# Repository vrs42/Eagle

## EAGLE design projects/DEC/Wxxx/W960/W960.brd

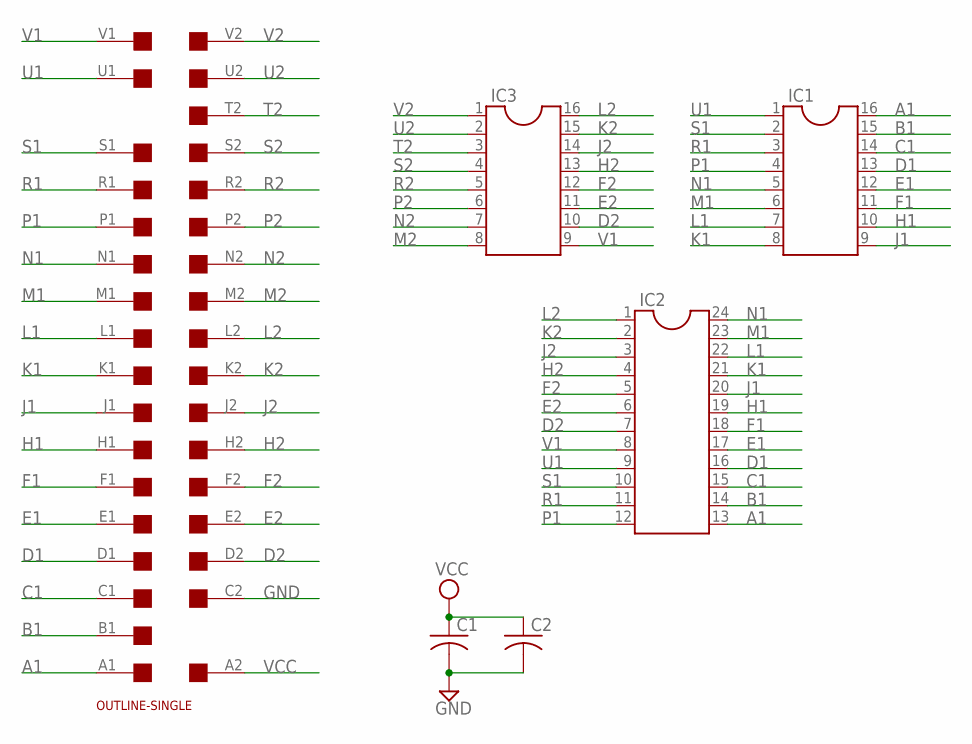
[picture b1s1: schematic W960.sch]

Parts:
C1, C2: C-US050-025X075; C050-025X075
IC1, IC3: DIL16
IC2: DIL24-6
U$1: EDGE-2CONNECTOR; EDGE-CON2
U$2: OUTLINE-SINGLE; SINGLE

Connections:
A1: IC1.16, IC2.13, U$1.A1
B1: IC1.15, IC2.14, U$1.B1
C1: IC1.14, IC2.15, U$1.C1
D1: IC1.13, IC2.16, U$1.D1
D2: IC2.7, IC3.10, U$1.D2
E1: IC1.12, IC2.17, U$1.E1
E2: IC2.6, IC3.11, U$1.E2
F1: IC1.11, IC2.18, U$1.F1
F2: IC2.5, IC3.12, U$1.F2
GND: C1.2, C2.2, U$1.C2
H1: IC1.10, IC2.19, U$1.H1
H2: IC2.4, IC3.13, U$1.H2
J1: IC1.9, IC2.20, U$1.J1
J2: IC2.3, IC3.14, U$1.J2
K1: IC1.8, IC2.21, U$1.K1
K2: IC2.2, IC3.15, U$1.K2
L1: IC1.7, IC2.22, U$1.L1
L2: IC2.1, IC3.16, U$1.L2
M1: IC1.6, IC2.23, U$1.M1
M2: IC3.8, U$1.M2
N1: IC1.5, IC2.24, U$1.N1
N2: IC3.7, U$1.N2
P1: IC1.4, IC2.12, U$1.P1
P2: IC3.6, U$1.P2
R1: IC1.3, IC2.11, U$1.R1
R2: IC3.5, U$1.R2
S1: IC1.2, IC2.10, U$1.S1
S2: IC3.4, U$1.S2
T2: IC3.3, U$1.T2
U1: IC1.1, IC2.9, U$1.U1
U2: IC3.2, U$1.U2
V1: IC2.8, IC3.9, U$1.V1
V2: IC3.1, U$1.V2
VCC: C1.1, C2.1, U$1.A2

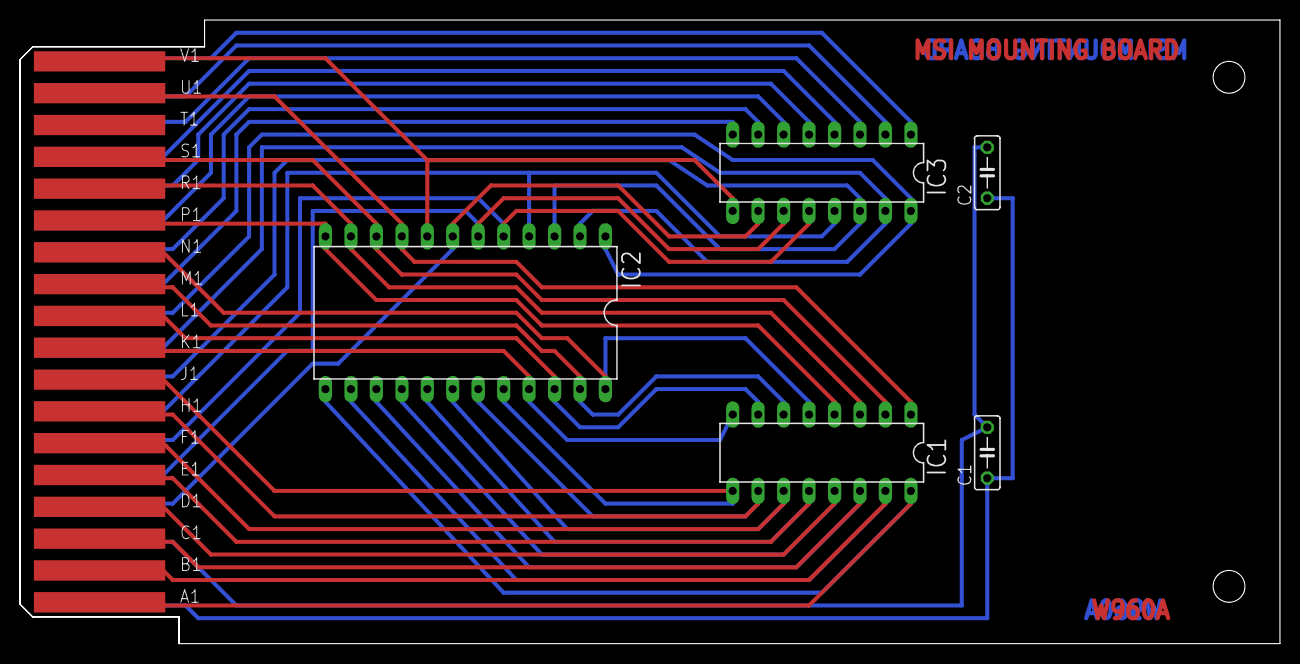
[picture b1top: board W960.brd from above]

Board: 2 copper layers, 125.7 x 62.2 mm, 7 parts (0 on the bottom side), 34 nets.

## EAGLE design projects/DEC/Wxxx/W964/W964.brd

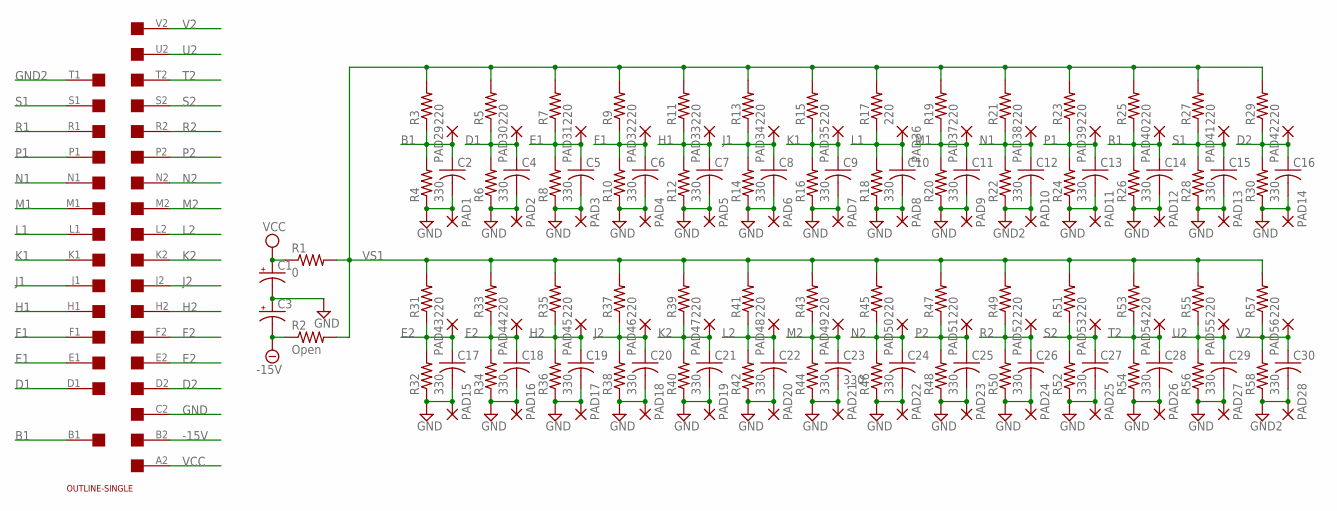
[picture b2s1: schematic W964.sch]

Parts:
C1, C3: CPOL-USE22-6AXIAL; E22-6
C2, C4, C5, C6, C7, C8, C9, C10, C11, C12, C13, C14, C15, C16, C17, C18, C19, C20, C21, C22, C24, C25, C26, C27, C28, C29, C30: C-US050-025X075; C050-025X075
C23: 330; C050-025X075
PAD1, PAD2, PAD3, PAD4, PAD5, PAD6, PAD7, PAD8, PAD9, PAD10, PAD11, PAD12, PAD13, PAD14, PAD15, PAD16, PAD17, PAD18, PAD19, PAD20, PAD21, PAD22, PAD23, PAD24, PAD25, PAD26, PAD27, PAD28, PAD29, PAD30, PAD31, PAD32, PAD33, PAD34, PAD35, PAD36, PAD37, PAD38, PAD39, PAD40, PAD41, PAD42, PAD43, PAD44, PAD45, PAD46, PAD47, PAD48, PAD49, PAD50, PAD51, PAD52, PAD53, PAD54, PAD55, PAD56: 1,6/0,9
R1: 0; 0207/10
R2: Open; 0207/10
R3, R5, R7, R9, R11, R13, R15, R17, R19, R21, R23, R25, R27, R29, R31, R33, R35, R37, R39, R41, R43, R45, R47, R49, R51, R53, R55, R57: 220; 0207/10
R4, R6, R8, R10, R12, R14, R16, R18, R20, R22, R24, R26, R28, R30, R32, R34, R36, R38, R40, R42, R44, R46, R48, R50, R52, R54, R56, R58: 330; 0207/10
U$1: EDGE-2CONNECTOR; EDGE-CON2
U$2: OUTLINE-SINGLE; SINGLE

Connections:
-15V: C3.-, R2.1, U$1.B2
B1: C2.1, PAD29.1, R3.1, R4.2, U$1.B1
D1: C4.1, PAD30.1, R5.1, R6.2, U$1.D1
D2: C16.1, PAD42.1, R29.1, R30.2, U$1.D2
E1: C5.1, PAD31.1, R7.1, R8.2, U$1.E1
E2: C17.1, PAD43.1, R31.1, R32.2, U$1.E2
F1: C6.1, PAD32.1, R9.1, R10.2, U$1.F1
F2: C18.1, PAD44.1, R33.1, R34.2, U$1.F2
GND: C1.-, C2.2, C3.+, C4.2, C5.2, C6.2, C7.2, C8.2, C9.2, C10.2, C11.2, C13.2, C14.2, C15.2, C16.2, C17.2, C18.2, C19.2, C20.2, C21.2, C22.2, C23.2, C24.2, C25.2, C26.2, C27.2, C28.2, C29.2, PAD1.1, PAD2.1, PAD3.1, PAD4.1, PAD5.1, PAD6.1, PAD7.1, PAD8.1, PAD9.1, PAD11.1, PAD12.1, PAD13.1, PAD14.1, PAD15.1, PAD16.1, PAD17.1, PAD18.1, PAD19.1, PAD20.1, PAD21.1, PAD22.1, PAD23.1, PAD24.1, PAD25.1, PAD26.1, PAD27.1, R4.1, R6.1, R8.1, R10.1, R12.1, R14.1, R16.1, R18.1, R20.1, R24.1, R26.1, R28.1, R30.1, R32.1, R34.1, R36.1, R38.1, R40.1, R42.1, R44.1, R46.1, R48.1, R50.1, R52.1, R54.1, R56.1, U$1.C2
GND2: C12.2, C30.2, PAD10.1, PAD28.1, R22.1, R58.1, U$1.T1
H1: C7.1, PAD33.1, R11.1, R12.2, U$1.H1
H2: C19.1, PAD45.1, R35.1, R36.2, U$1.H2
J1: C8.1, PAD34.1, R13.1, R14.2, U$1.J1
J2: C20.1, PAD46.1, R37.1, R38.2, U$1.J2
K1: C9.1, PAD35.1, R15.1, R16.2, U$1.K1
K2: C21.1, PAD47.1, R39.1, R40.2, U$1.K2
L1: C10.1, PAD36.1, R17.1, R18.2, U$1.L1
L2: C22.1, PAD48.1, R41.1, R42.2, U$1.L2
M1: C11.1, PAD37.1, R19.1, R20.2, U$1.M1
M2: C23.1, PAD49.1, R43.1, R44.2, U$1.M2
N1: C12.1, PAD38.1, R21.1, R22.2, U$1.N1
N2: C24.1, PAD50.1, R45.1, R46.2, U$1.N2
P1: C13.1, PAD39.1, R23.1, R24.2, U$1.P1
P2: C25.1, PAD51.1, R47.1, R48.2, U$1.P2
R1: C14.1, PAD40.1, R25.1, R26.2, U$1.R1
R2: C26.1, PAD52.1, R49.1, R50.2, U$1.R2
S1: C15.1, PAD41.1, R27.1, R28.2, U$1.S1
S2: C27.1, PAD53.1, R51.1, R52.2, U$1.S2
T2: C28.1, PAD54.1, R53.1, R54.2, U$1.T2
U2: C29.1, PAD55.1, R55.1, R56.2, U$1.U2
V2: C30.1, PAD56.1, R57.1, R58.2, U$1.V2
VCC: C1.+, R1.1, U$1.A2
VS1: R1.2, R2.2, R3.2, R5.2, R7.2, R9.2, R11.2, R13.2, R15.2, R17.2, R19.2, R21.2, R23.2, R25.2, R27.2, R29.2, R31.2, R33.2, R35.2, R37.2, R39.2, R41.2, R43.2, R45.2, R47.2, R49.2, R51.2, R53.2, R55.2, R57.2

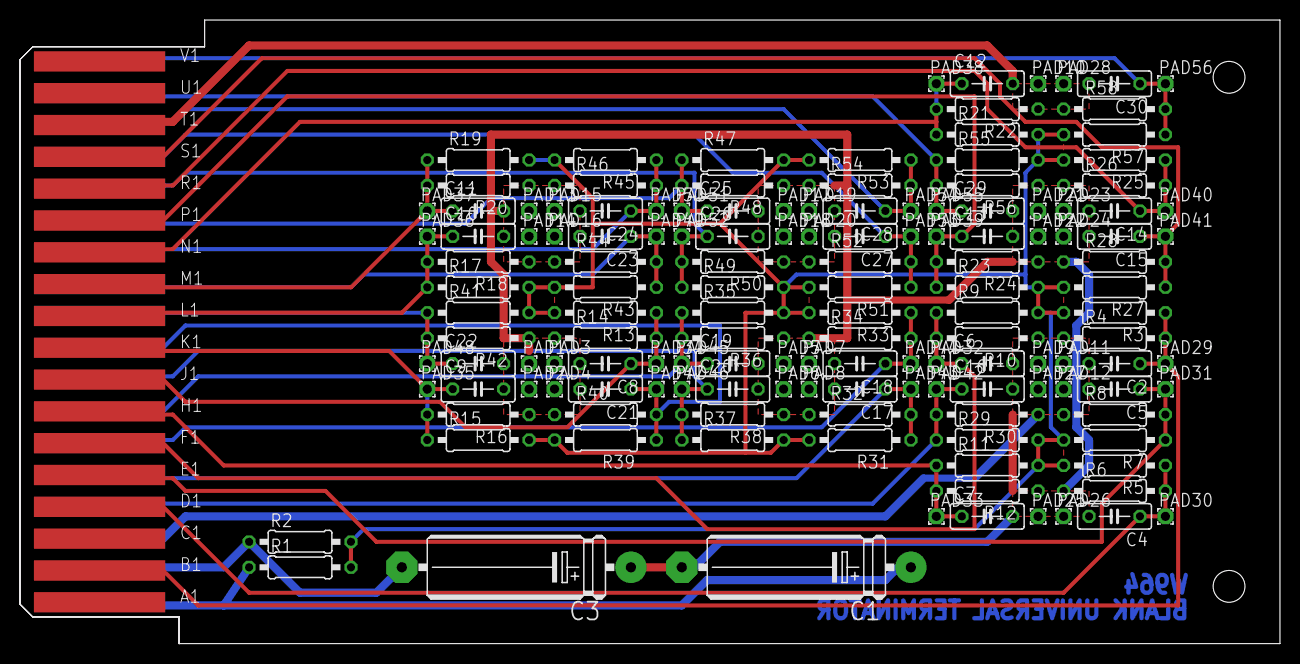
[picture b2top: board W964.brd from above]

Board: 2 copper layers, 125.7 x 62.2 mm, 146 parts (0 on the bottom side), 33 nets.

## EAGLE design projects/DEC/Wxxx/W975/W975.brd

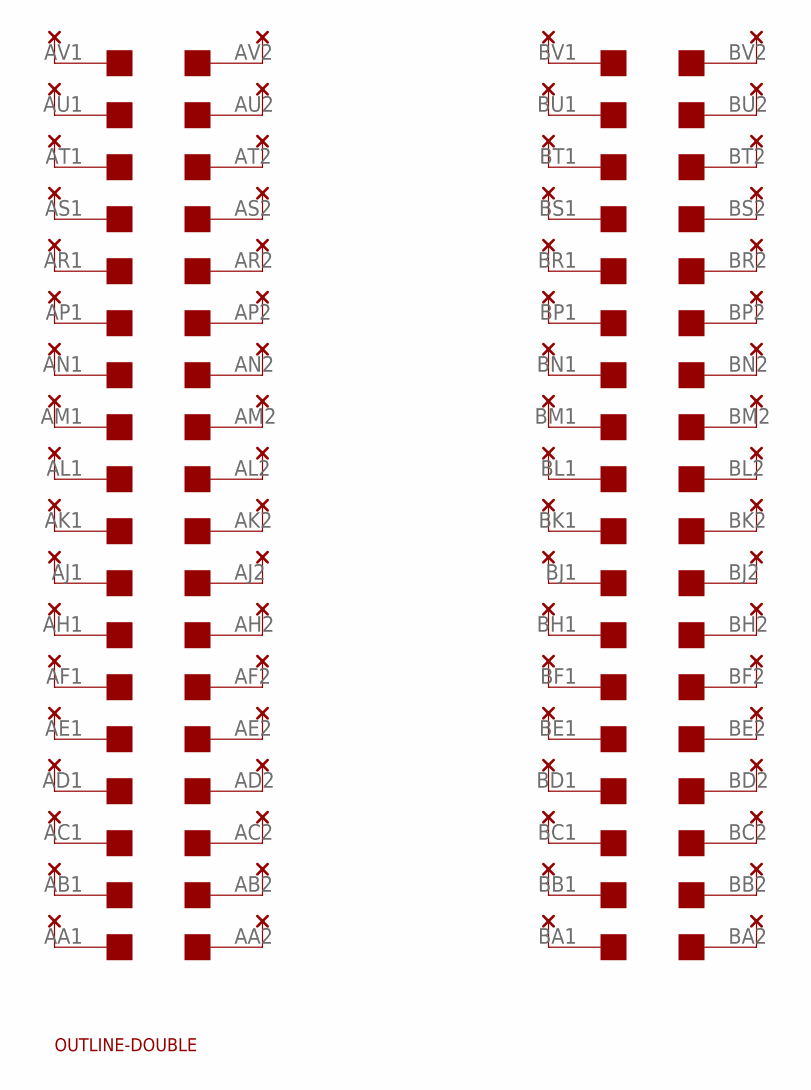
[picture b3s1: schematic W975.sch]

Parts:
A: A; THRU-HOLE2
B: B; THRU-HOLE2
U$1: OUTLINE-DOUBLE; DOUBLE
U$2: DOUBLE; EDGE-CON4

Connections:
unnamed: A.K2, U$2.AK2
unnamed: A.J2, U$2.AJ2
unnamed: A.H2, U$2.AH2
unnamed: A.L2, U$2.AL2
unnamed: A.M2, U$2.AM2
unnamed: A.N2, U$2.AN2
unnamed: A.P2, U$2.AP2
unnamed: A.F2, U$2.AF2
unnamed: A.E2, U$2.AE2
unnamed: A.D2, U$2.AD2
unnamed: A.C2, U$2.AC2
unnamed: A.R2, U$2.AR2
unnamed: A.S2, U$2.AS2
unnamed: A.B2, U$2.AB2
unnamed: A.A2, U$2.AA2
unnamed: A.T2, U$2.AT2
unnamed: A.U2, U$2.AU2
unnamed: A.V2, U$2.AV2
unnamed: A.A1, U$2.AA1
unnamed: A.V1, U$2.AV1
unnamed: A.U1, U$2.AU1
unnamed: A.T1, U$2.AT1
unnamed: A.S1, U$2.AS1
unnamed: A.R1, U$2.AR1
unnamed: A.P1, U$2.AP1
unnamed: A.N1, U$2.AN1
unnamed: A.M1, U$2.AM1
unnamed: A.L1, U$2.AL1
unnamed: A.K1, U$2.AK1
unnamed: A.J1, U$2.AJ1
unnamed: A.H1, U$2.AH1
unnamed: A.F1, U$2.AF1
unnamed: A.E1, U$2.AE1
unnamed: A.D1, U$2.AD1
unnamed: A.C1, U$2.AC1
unnamed: A.B1, U$2.AB1
unnamed: B.K2, U$2.BK2
unnamed: B.J2, U$2.BJ2
unnamed: B.H2, U$2.BH2
unnamed: B.L2, U$2.BL2
unnamed: B.M2, U$2.BM2
unnamed: B.N2, U$2.BN2
unnamed: B.P2, U$2.BP2
unnamed: B.F2, U$2.BF2
unnamed: B.E2, U$2.BE2
unnamed: B.D2, U$2.BD2
unnamed: B.C2, U$2.BC2
unnamed: B.R2, U$2.BR2
unnamed: B.S2, U$2.BS2
unnamed: B.B2, U$2.BB2
unnamed: B.A2, U$2.BA2
unnamed: B.T2, U$2.BT2
unnamed: B.U2, U$2.BU2
unnamed: B.V2, U$2.BV2
unnamed: B.A1, U$2.BA1
unnamed: B.V1, U$2.BV1
unnamed: B.U1, U$2.BU1
unnamed: B.T1, U$2.BT1
unnamed: B.S1, U$2.BS1
unnamed: B.R1, U$2.BR1
unnamed: B.P1, U$2.BP1
unnamed: B.N1, U$2.BN1
unnamed: B.M1, U$2.BM1
unnamed: B.L1, U$2.BL1
unnamed: B.K1, U$2.BK1
unnamed: B.J1, U$2.BJ1
unnamed: B.H1, U$2.BH1
unnamed: B.F1, U$2.BF1
unnamed: B.E1, U$2.BE1
unnamed: B.D1, U$2.BD1
unnamed: B.C1, U$2.BC1
unnamed: B.B1, U$2.BB1

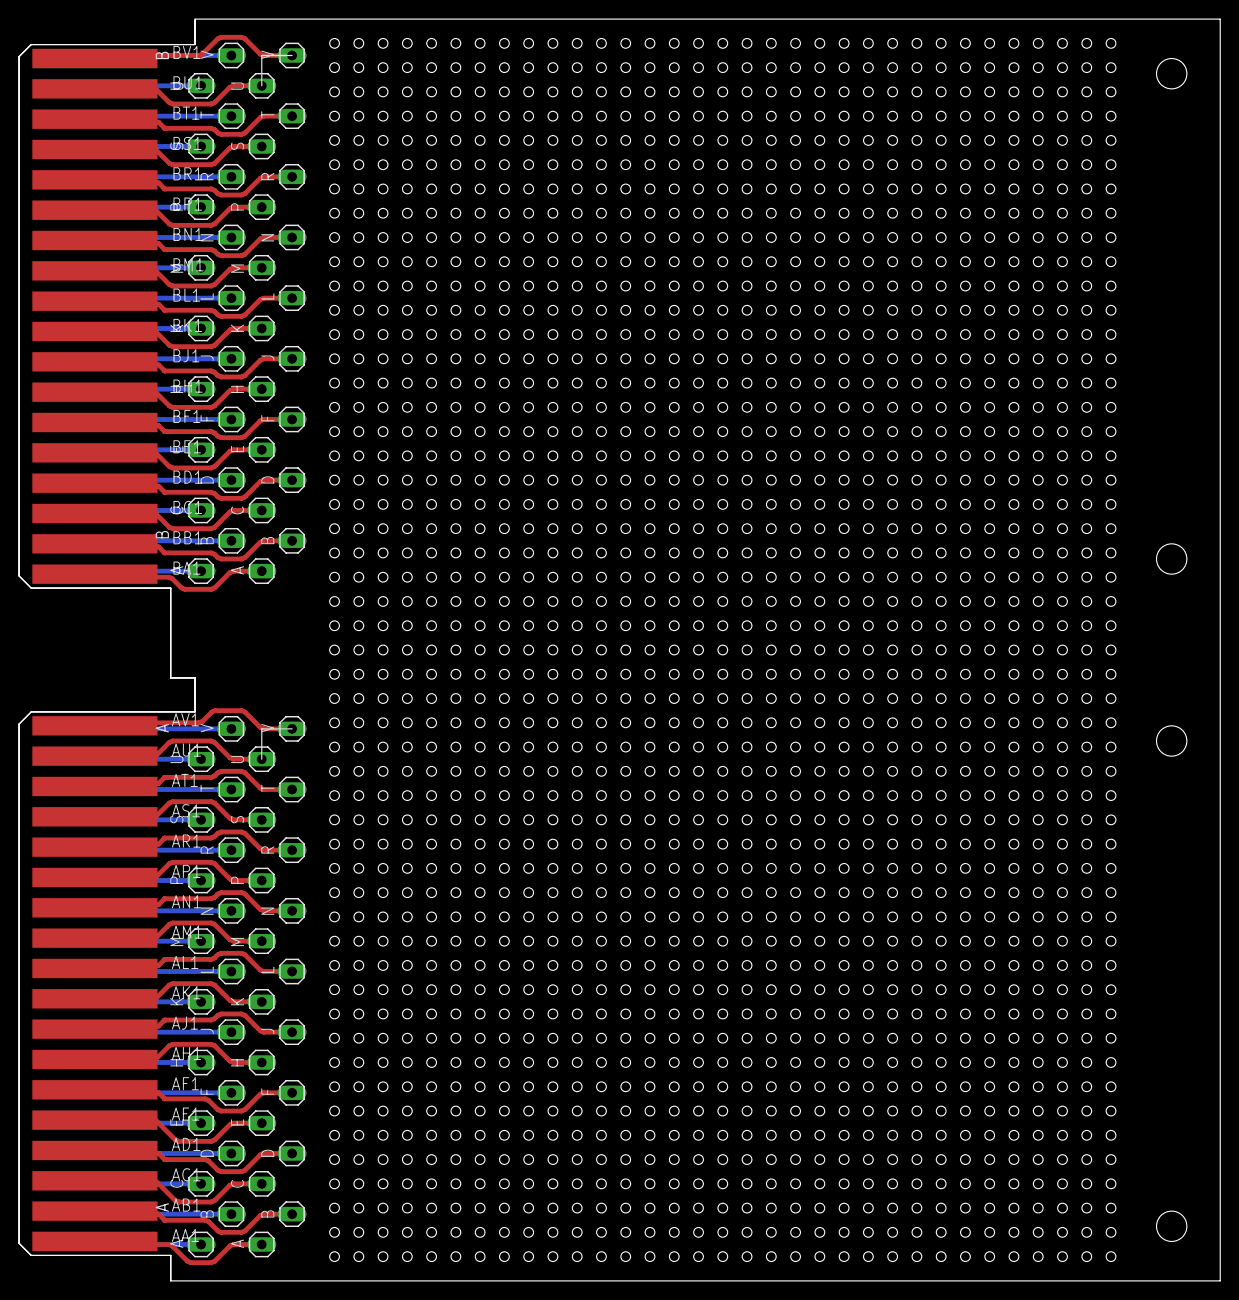
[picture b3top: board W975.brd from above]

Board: 2 copper layers, 125.7 x 132.1 mm, 4 parts (0 on the bottom side), 72 nets.

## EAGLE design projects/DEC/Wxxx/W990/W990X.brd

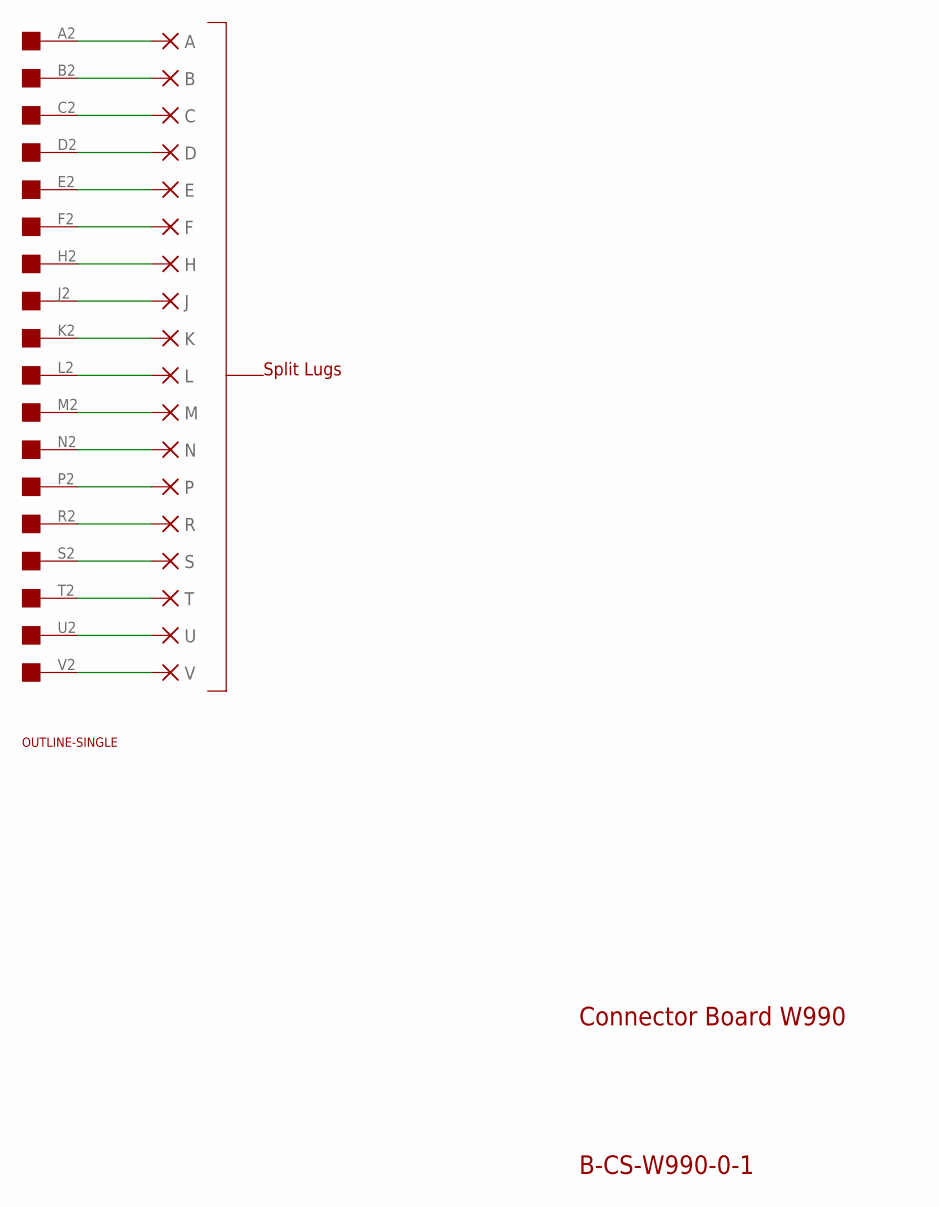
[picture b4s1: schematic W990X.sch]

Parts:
A: PAD-0465; 0465
B: PAD-0465; 0465
C: PAD-0465; 0465
D: PAD-0465; 0465
E: PAD-0465; 0465
F: PAD-0465; 0465
H: PAD-0465; 0465
J: PAD-0465; 0465
K: PAD-0465; 0465
L: PAD-0465; 0465
M: PAD-0465; 0465
N: PAD-0465; 0465
P: PAD-0465; 0465
R: PAD-0465; 0465
S: PAD-0465; 0465
T: PAD-0465; 0465
U: PAD-0465; 0465
U$2: OUTLINE-SINGLE; SINGLE
U$4: EDGE-1; EDGE-CON1
V: PAD-0465; 0465

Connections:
unnamed: E.P$1, U$4.E2
unnamed: H.P$1, U$4.H2
unnamed: K.P$1, U$4.K2
unnamed: M.P$1, U$4.M2
unnamed: P.P$1, U$4.P2
unnamed: S.P$1, U$4.S2
unnamed: T.P$1, U$4.T2
unnamed: B.P$1, U$4.B2
unnamed: D.P$1, U$4.D2
unnamed: A.P$1, U$4.A2
unnamed: U$4.V2, V.P$1
unnamed: C.P$1, U$4.C2
unnamed: F.P$1, U$4.F2
unnamed: J.P$1, U$4.J2
unnamed: L.P$1, U$4.L2
unnamed: N.P$1, U$4.N2
unnamed: R.P$1, U$4.R2
unnamed: U.P$1, U$4.U2

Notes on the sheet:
Connector Board W990
B-CS-W990-0-1
Split Lugs

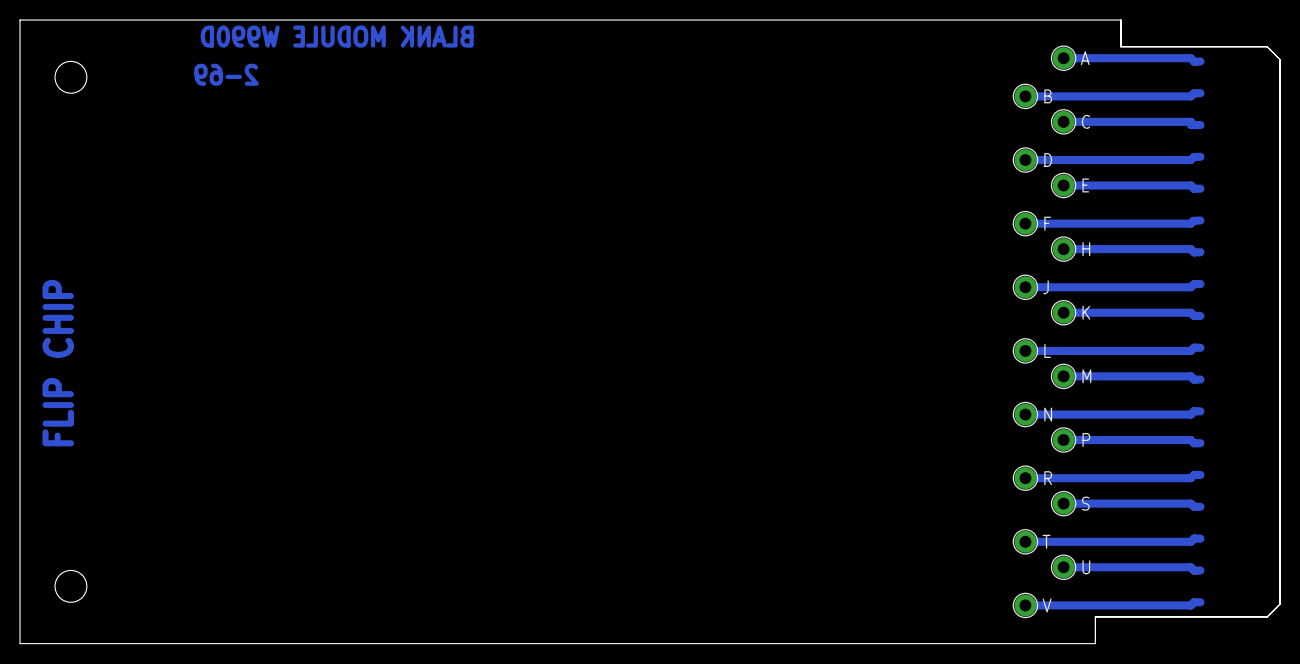
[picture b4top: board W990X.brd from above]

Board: 2 copper layers, 125.7 x 62.2 mm, 20 parts (0 on the bottom side), 18 nets.

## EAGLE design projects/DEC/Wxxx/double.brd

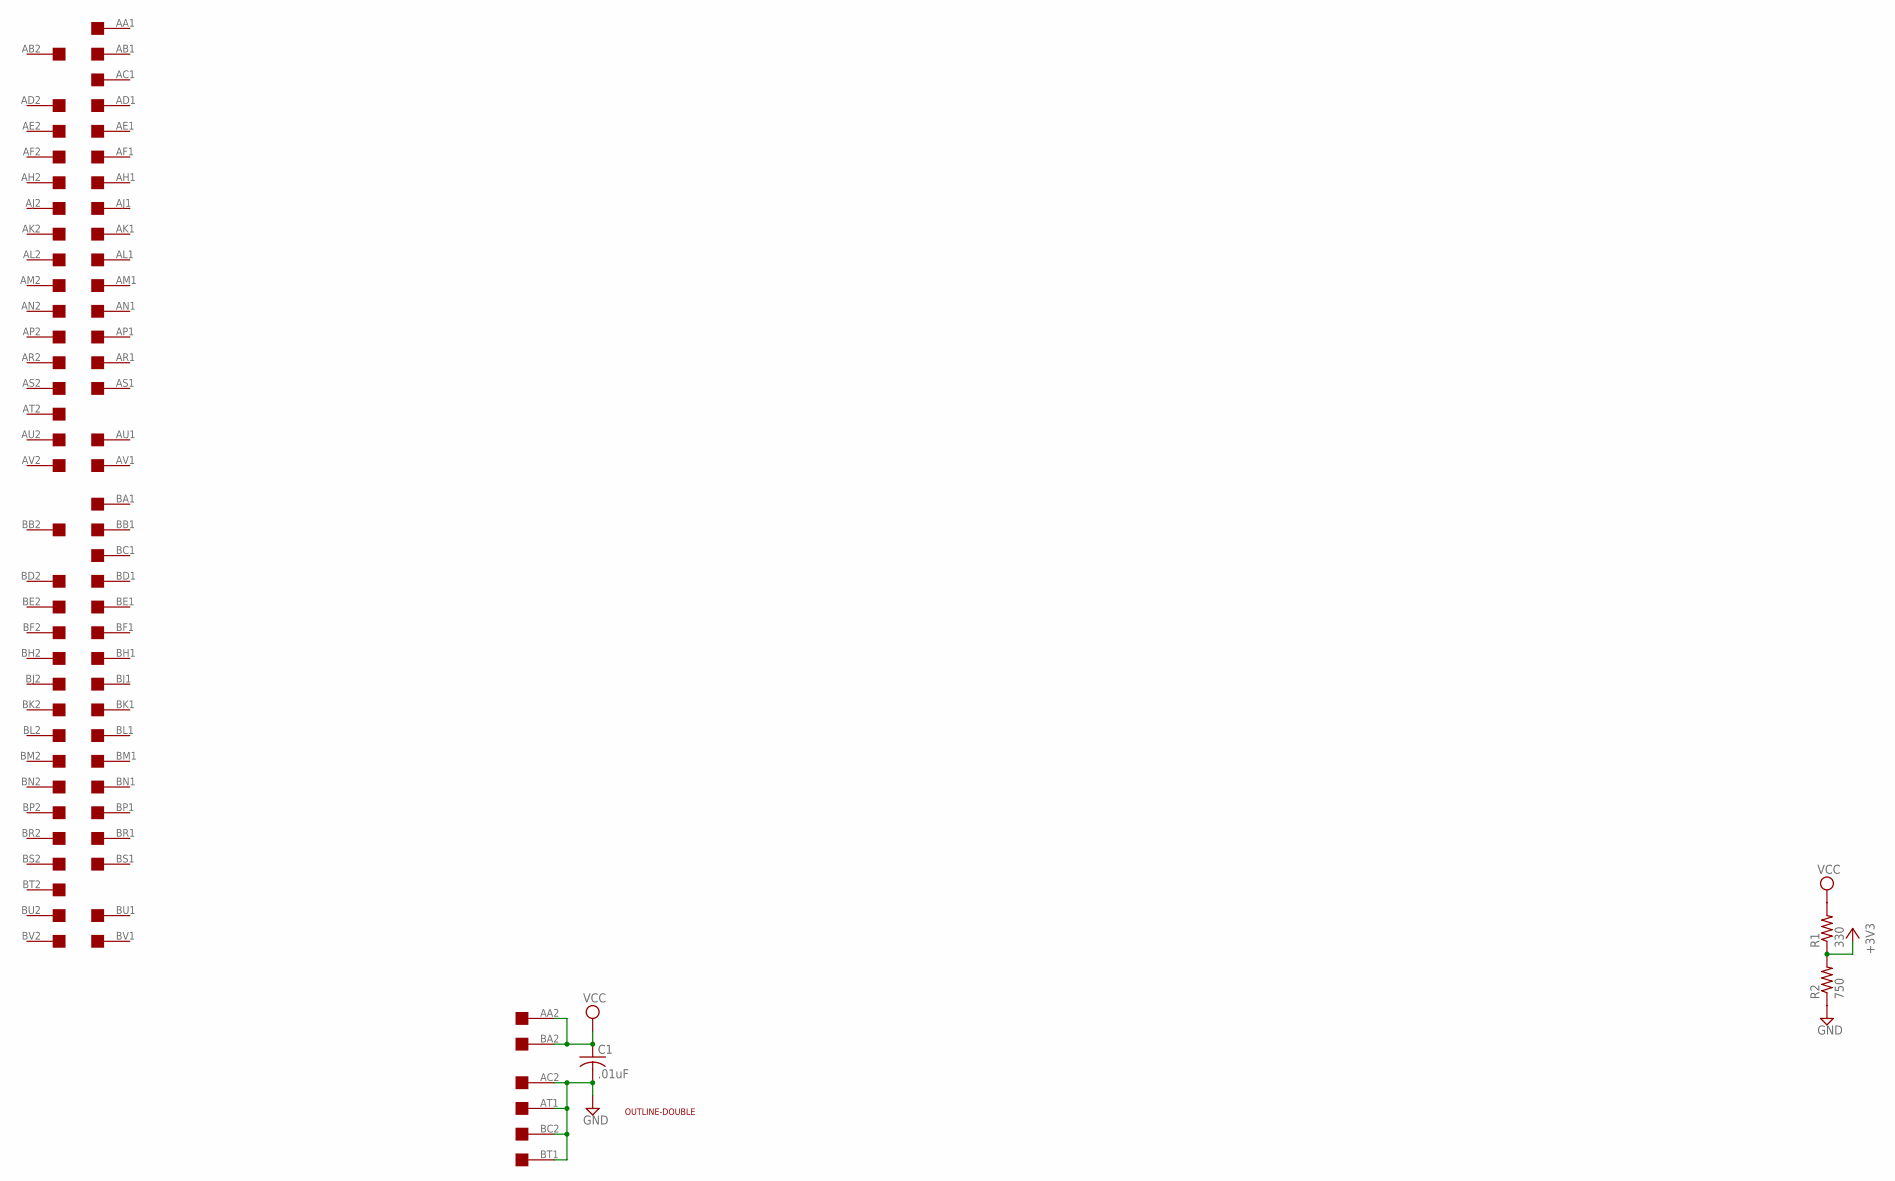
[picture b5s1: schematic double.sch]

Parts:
C1: .01uF; C050-025X075
R1: 330; 0207/10
R2: 750; 0207/10
U$1: OUTLINE-DOUBLE; DOUBLE
U$3: DOUBLE; EDGE-CON4

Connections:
+3V3: R1.1, R2.2
GND: C1.2, R2.1, U$3.AC2, U$3.AT1, U$3.BC2, U$3.BT1
VCC: C1.1, R1.2, U$3.AA2, U$3.BA2

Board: 2 copper layers, 5 parts (0 on the bottom side), 3 nets, no tracks yet.

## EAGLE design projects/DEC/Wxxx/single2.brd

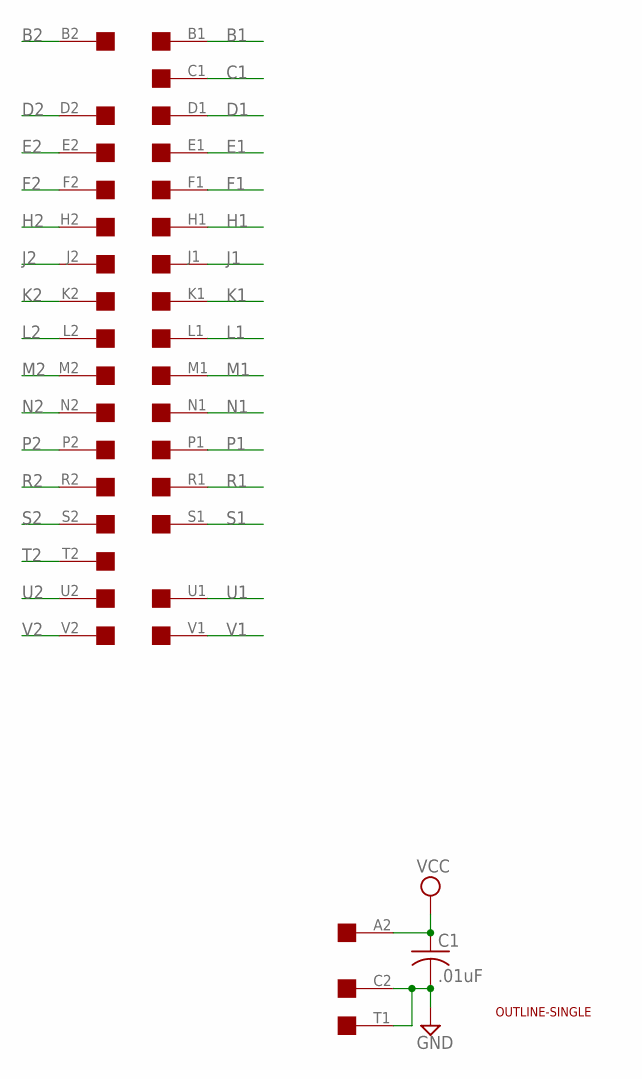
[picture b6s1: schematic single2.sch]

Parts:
C1: .01uF; C063-025X075
U$1: OUTLINE-SINGLE; SINGLE
U$2: SINGLE; EDGE-CON2

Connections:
B1: U$2.B1
B2: U$2.B2
C1: U$2.C1
D1: U$2.D1
D2: U$2.D2
E1: U$2.E1
E2: U$2.E2
F1: U$2.F1
F2: U$2.F2
GND: C1.2, U$2.C2, U$2.T1
H1: U$2.H1
H2: U$2.H2
J1: U$2.J1
J2: U$2.J2
K1: U$2.K1
K2: U$2.K2
L1: U$2.L1
L2: U$2.L2
M1: U$2.M1
M2: U$2.M2
N1: U$2.N1
N2: U$2.N2
P1: U$2.P1
P2: U$2.P2
R1: U$2.R1
R2: U$2.R2
S1: U$2.S1
S2: U$2.S2
T2: U$2.T2
U1: U$2.U1
U2: U$2.U2
V1: U$2.V1
V2: U$2.V2
VCC: C1.1, U$2.A2

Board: 2 copper layers, 3 parts (0 on the bottom side), 2 nets, no tracks yet.
